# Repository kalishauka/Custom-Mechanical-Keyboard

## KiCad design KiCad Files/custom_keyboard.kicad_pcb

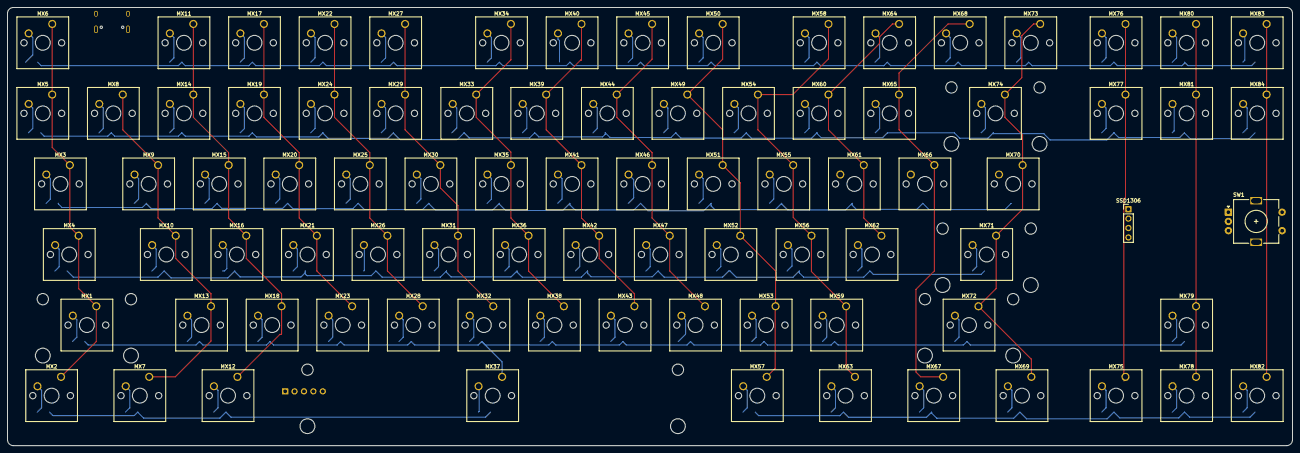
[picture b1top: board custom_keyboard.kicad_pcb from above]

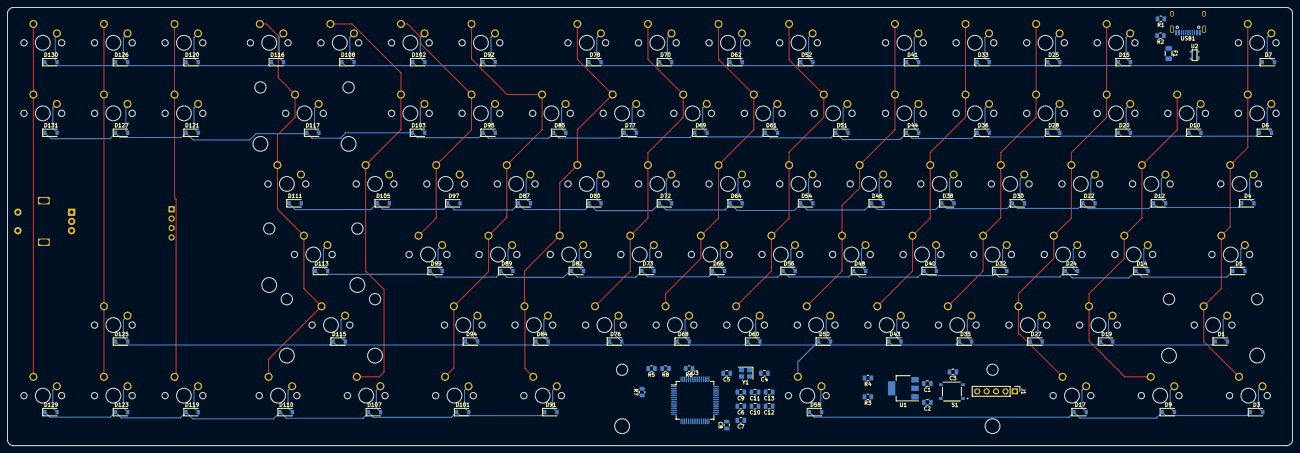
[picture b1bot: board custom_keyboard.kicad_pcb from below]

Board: 2 copper layers, 346.9 x 118.3 mm, 199 parts (113 on the bottom side), 130 nets.

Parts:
C1, C2: 10u; C_0805_2012Metric
C3: 0.1u; C_0805_2012Metric
C4, C5: 22p; C_0805_2012Metric
C6, C8: 4.7u; C_0805_2012Metric
C7, C9, C10, C11, C12, C13: 100n; C_0805_2012Metric
D1, D3, D4, D5, D6, D7, D9, D10, D12, D14, D15, D17, D19, D20, D22, D24, D25, D27, D28, D30, D32, D33, D35, D36, D38, D40, D41, D43, D44, D46, D48, D50, D51, D52, D54, D56, D58, D60, D61, D62, D64, D66, D68, D69, D70, D72, D73, D76, D77, D78, D80, D82, D84, D85, D87, D89, D91, D92, D94, D95, D97, D99, D101, D102, D103, D105, D107, D108, D110, D111, D113, D115, D116, D117, D119, D120, D121, D123, D125, D126, D127, D129, D130, D131: D_Small; D_SOD-123
F1: 500m; Fuse_1206_3216Metric
J1: Conn_01x05_Male; PinHeader_1x05_P2.54mm_Vertical
MX1: MX-NoLED L SHIFT; SW_Cherry_MX_2.25u_PCB
MX2: MX-NoLED CRTL; SW_Cherry_MX_1.25u_PCB
MX3: MX-NoLED Tab; SW_Cherry_MX_1.50u_PCB
MX4: MX-NoLED CAPS; SW_Cherry_MX_1.75u_PCB
MX5: MX-NoLED tilde; SW_Cherry_MX_1.00u_PCB
MX6: MX-NoLED ESC; SW_Cherry_MX_1.00u_PCB
MX7, MX63: MX-NoLED WIN; SW_Cherry_MX_1.25u_PCB
MX8: MX-NoLED 1; SW_Cherry_MX_1.00u_PCB
MX9: MX-NoLED Q; SW_Cherry_MX_1.00u_PCB
MX10: MX-NoLED A; SW_Cherry_MX_1.00u_PCB
MX11: MX-NoLED F1; SW_Cherry_MX_1.00u_PCB
MX12, MX57: MX-NoLED ALT; SW_Cherry_MX_1.25u_PCB
MX13: MX-NoLED Z; SW_Cherry_MX_1.00u_PCB
MX14: MX-NoLED 2; SW_Cherry_MX_1.00u_PCB
MX15: MX-NoLED W; SW_Cherry_MX_1.00u_PCB
MX16: MX-NoLED S; SW_Cherry_MX_1.00u_PCB
MX17: MX-NoLED F2; SW_Cherry_MX_1.00u_PCB
MX18: MX-NoLED X; SW_Cherry_MX_1.00u_PCB
MX19: MX-NoLED 3; SW_Cherry_MX_1.00u_PCB
MX20: MX-NoLED E; SW_Cherry_MX_1.00u_PCB
MX21: MX-NoLED D; SW_Cherry_MX_1.00u_PCB
MX22: MX-NoLED F3; SW_Cherry_MX_1.00u_PCB
MX23: MX-NoLED C; SW_Cherry_MX_1.00u_PCB
MX24: MX-NoLED 4; SW_Cherry_MX_1.00u_PCB
MX25: MX-NoLED R; SW_Cherry_MX_1.00u_PCB
MX26: MX-NoLED F; SW_Cherry_MX_1.00u_PCB
MX27: MX-NoLED F4; SW_Cherry_MX_1.00u_PCB
MX28: MX-NoLED V; SW_Cherry_MX_1.00u_PCB
MX29: MX-NoLED 5; SW_Cherry_MX_1.00u_PCB
MX30: MX-NoLED T; SW_Cherry_MX_1.00u_PCB
MX31: MX-NoLED G; SW_Cherry_MX_1.00u_PCB
MX32: MX-NoLED B; SW_Cherry_MX_1.00u_PCB
MX33: MX-NoLED 6; SW_Cherry_MX_1.00u_PCB
MX34: MX-NoLED F5; SW_Cherry_MX_1.00u_PCB
MX35: MX-NoLED Y; SW_Cherry_MX_1.00u_PCB
MX36: MX-NoLED H; SW_Cherry_MX_1.00u_PCB
MX37: MX-NoLED SPACE; SW_Cherry_MX_6.25u_PCB
MX38: MX-NoLED N; SW_Cherry_MX_1.00u_PCB
MX39: MX-NoLED 7; SW_Cherry_MX_1.00u_PCB
MX40: MX-NoLED F6; SW_Cherry_MX_1.00u_PCB
MX41: MX-NoLED U; SW_Cherry_MX_1.00u_PCB
MX42: MX-NoLED J; SW_Cherry_MX_1.00u_PCB
MX43: MX-NoLED M; SW_Cherry_MX_1.00u_PCB
MX44: MX-NoLED 8; SW_Cherry_MX_1.00u_PCB
MX45: MX-NoLED F7; SW_Cherry_MX_1.00u_PCB
MX46: MX-NoLED I; SW_Cherry_MX_1.00u_PCB
MX47: MX-NoLED K; SW_Cherry_MX_1.00u_PCB
MX48: MX-NoLED ,; SW_Cherry_MX_1.00u_PCB
MX49: MX-NoLED 9; SW_Cherry_MX_1.00u_PCB
MX50: MX-NoLED F8; SW_Cherry_MX_1.00u_PCB
MX51: MX-NoLED O; SW_Cherry_MX_1.00u_PCB
MX52: MX-NoLED L; SW_Cherry_MX_1.00u_PCB
MX53: MX-NoLED .; SW_Cherry_MX_1.00u_PCB
MX54: MX-NoLED 0; SW_Cherry_MX_1.00u_PCB
MX55: MX-NoLED P; SW_Cherry_MX_1.00u_PCB
MX56: MX-NoLED ;; SW_Cherry_MX_1.00u_PCB
MX58: MX-NoLED F9; SW_Cherry_MX_1.00u_PCB
MX59: MX-NoLED /; SW_Cherry_MX_1.00u_PCB
MX60: MX-NoLED dash; SW_Cherry_MX_1.00u_PCB
MX61: MX-NoLED [; SW_Cherry_MX_1.00u_PCB
MX62: MX-NoLED '; SW_Cherry_MX_1.00u_PCB
MX64: MX-NoLED F10; SW_Cherry_MX_1.00u_PCB
MX65: MX-NoLED =; SW_Cherry_MX_1.00u_PCB
MX66: MX-NoLED ]; SW_Cherry_MX_1.00u_PCB
MX67: MX-NoLED MENU; SW_Cherry_MX_1.25u_PCB
MX68: MX-NoLED F11; SW_Cherry_MX_1.00u_PCB
MX69: MX-NoLED CTRL; SW_Cherry_MX_1.25u_PCB
MX70: MX-NoLED \; SW_Cherry_MX_1.50u_PCB
MX71: MX-NoLED ENTER; SW_Cherry_MX_2.25u_PCB
MX72: MX-NoLED R SHIFT; SW_Cherry_MX_2.75u_PCB
MX73: MX-NoLED F12; SW_Cherry_MX_1.00u_PCB
MX74: MX-NoLED BACKSPACE; SW_Cherry_MX_2.00u_PCB
MX75: MX-NoLED LEFT; SW_Cherry_MX_1.00u_PCB
MX76: MX-NoLED Insert; SW_Cherry_MX_1.00u_PCB
MX77: MX-NoLED Delete; SW_Cherry_MX_1.00u_PCB
MX78: MX-NoLED DOWN; SW_Cherry_MX_1.00u_PCB
MX79: MX-NoLED UP; SW_Cherry_MX_1.00u_PCB
MX80: MX-NoLED Home; SW_Cherry_MX_1.00u_PCB
MX81: MX-NoLED End; SW_Cherry_MX_1.00u_PCB
MX82: MX-NoLED RIGHT; SW_Cherry_MX_1.00u_PCB
MX83: MX-NoLED PgUp; SW_Cherry_MX_1.00u_PCB
MX84: MX-NoLED PgDn; SW_Cherry_MX_1.00u_PCB
R1, R2: 5.1k; R_0805_2012Metric
R3, R4: 0; R_0805_2012Metric
R5: 4.7k; R_0805_2012Metric
R6: 10k; R_0805_2012Metric
R7, R8: 22; R_0805_2012Metric
S1: TS-1187A-B-A-B; SW_TS-1187A-B-A-B
SSD1306: Conn_01x04_Male; PinHeader_1x04_P2.54mm_Vertical
SW1: RotaryEncoder_Switch; RotaryEncoder_Alps_EC11E-Switch_Vertical_H20mm
U1: AMS1117; SOT-223-3_TabPin2
U2: PRTR5V0U2X; SOT143B
U3: STM32F401RCTx; LQFP-64_10x10mm_P0.5mm
USB1: HRO-TYPE-C-31-M-12
Y1: 16MHz; Crystal_SMD_3225-4Pin_3.2x2.5mm

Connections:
+3V3: C2.1, C6.1, C7.1, C9.1, C10.1, C11.1, C12.1, C13.1, J1.4, R3.1, R5.1, R6.1, SSD1306.2, U1.2 (VO), U3.1 (VBAT), U3.19 (VDD), U3.32 (VDD), U3.48 (VDD), U3.64 (VDD)
+5V: C1.1, F1.1, U1.3 (VI)
Col1: MX1.1 (COL), MX2.1 (COL), MX3.1 (COL), MX4.1 (COL), MX5.1 (COL), MX6.1 (COL), U3.37 (PC6)
Col2: MX7.1 (COL), MX8.1 (COL), MX9.1 (COL), MX10.1 (COL), MX13.1 (COL), U3.38 (PC7)
Col3: MX11.1 (COL), MX12.1 (COL), MX14.1 (COL), MX15.1 (COL), MX16.1 (COL), MX18.1 (COL), U3.39 (PC8)
Col4: MX17.1 (COL), MX19.1 (COL), MX20.1 (COL), MX21.1 (COL), MX23.1 (COL), U3.40 (PC9)
Col5: MX22.1 (COL), MX24.1 (COL), MX25.1 (COL), MX26.1 (COL), MX28.1 (COL), U3.51 (PC10)
Col6: MX27.1 (COL), MX29.1 (COL), MX30.1 (COL), MX31.1 (COL), MX32.1 (COL), U3.52 (PC11)
Col7: MX33.1 (COL), MX34.1 (COL), MX35.1 (COL), MX36.1 (COL), MX38.1 (COL), U3.53 (PC12)
Col8: MX39.1 (COL), MX40.1 (COL), MX41.1 (COL), MX42.1 (COL), MX43.1 (COL), U3.2 (PC13)
Col9: MX44.1 (COL), MX45.1 (COL), MX46.1 (COL), MX47.1 (COL), MX48.1 (COL), U3.3 (PC14)
Col10: MX49.1 (COL), MX50.1 (COL), MX51.1 (COL), MX52.1 (COL), MX53.1 (COL), MX57.1 (COL), U3.4 (PC15)
Col11: MX54.1 (COL), MX55.1 (COL), MX56.1 (COL), MX58.1 (COL), MX59.1 (COL), MX63.1 (COL), U3.14 (PA0)
Col12: MX60.1 (COL), MX61.1 (COL), MX62.1 (COL), MX64.1 (COL), U3.15 (PA1)
Col13: MX65.1 (COL), MX66.1 (COL), MX67.1 (COL), MX68.1 (COL), U3.16 (PA2)
Col14: MX69.1 (COL), MX70.1 (COL), MX71.1 (COL), MX72.1 (COL), MX73.1 (COL), MX74.1 (COL), U3.17 (PA3)
Col15: MX75.1 (COL), MX76.1 (COL), MX77.1 (COL), U3.20 (PA4)
Col16: MX78.1 (COL), MX79.1 (COL), MX80.1 (COL), MX81.1 (COL), U3.21 (PA5)
Col17: MX82.1 (COL), MX83.1 (COL), MX84.1 (COL), U3.22 (PA6)
D+: R8.2, U2.2 (IO1), USB1.6 (DP1), USB1.8 (DP2)
D-: R7.2, U2.3 (IO2), USB1.5 (DN2), USB1.7 (DN1)
ENC_A: SW1.A, U3.23 (PA7)
ENC_B: SW1.B, U3.41 (PA8)
ENC_SW: SW1.S1, U3.42 (PA9)
GND: C1.2, C2.2, C3.1, C4.1, C5.1, C6.2, C7.2, C8.2, C9.2, C10.2, C11.2, C12.2, C13.2, J1.1, R1.2, R2.2, R4.2, S1.A, S1.B, SSD1306.1, SW1.C, SW1.S2, U1.1 (ADJ), U2.1 (GND), U3.12 (VSSA), U3.18 (VSS), U3.31 (VSS), U3.47 (VSS), U3.63 (VSS), USB1.1 (GND), USB1.12 (GND), USB1.13 (SHIELD), Y1.2, Y1.4
unnamed: C5.2, U3.6 (PH1), Y1.3
unnamed: C8.1, U3.30 (VCAP1)
unnamed: D1.2 (A), MX1.2 (ROW)
unnamed: D3.2 (A), MX2.2 (ROW)
unnamed: D4.2 (A), MX3.2 (ROW)
unnamed: D5.2 (A), MX4.2 (ROW)
unnamed: D6.2 (A), MX5.2 (ROW)
unnamed: D7.2 (A), MX6.2 (ROW)
unnamed: D9.2 (A), MX7.2 (ROW)
unnamed: D10.2 (A), MX8.2 (ROW)
unnamed: D12.2 (A), MX9.2 (ROW)
unnamed: D14.2 (A), MX10.2 (ROW)
unnamed: D15.2 (A), MX11.2 (ROW)
unnamed: D17.2 (A), MX12.2 (ROW)
unnamed: D19.2 (A), MX13.2 (ROW)
unnamed: D20.2 (A), MX14.2 (ROW)
unnamed: D22.2 (A), MX15.2 (ROW)
unnamed: D24.2 (A), MX16.2 (ROW)
unnamed: D25.2 (A), MX17.2 (ROW)
unnamed: D27.2 (A), MX18.2 (ROW)
unnamed: D28.2 (A), MX19.2 (ROW)
unnamed: D30.2 (A), MX20.2 (ROW)
unnamed: D32.2 (A), MX21.2 (ROW)
unnamed: D33.2 (A), MX22.2 (ROW)
unnamed: D35.2 (A), MX23.2 (ROW)
unnamed: D36.2 (A), MX24.2 (ROW)
unnamed: D38.2 (A), MX25.2 (ROW)
unnamed: D40.2 (A), MX26.2 (ROW)
unnamed: D41.2 (A), MX27.2 (ROW)
unnamed: D43.2 (A), MX28.2 (ROW)
unnamed: D44.2 (A), MX29.2 (ROW)
unnamed: D46.2 (A), MX30.2 (ROW)
unnamed: D48.2 (A), MX31.2 (ROW)
unnamed: D50.2 (A), MX32.2 (ROW)
unnamed: D51.2 (A), MX33.2 (ROW)
unnamed: D52.2 (A), MX34.2 (ROW)
unnamed: D54.2 (A), MX35.2 (ROW)
unnamed: D56.2 (A), MX36.2 (ROW)
unnamed: D58.2 (A), MX37.2 (ROW)
unnamed: D60.2 (A), MX38.2 (ROW)
unnamed: D61.2 (A), MX39.2 (ROW)
unnamed: D62.2 (A), MX40.2 (ROW)
unnamed: D64.2 (A), MX41.2 (ROW)
unnamed: D66.2 (A), MX42.2 (ROW)
unnamed: D68.2 (A), MX43.2 (ROW)
unnamed: D69.2 (A), MX44.2 (ROW)
unnamed: D70.2 (A), MX45.2 (ROW)
unnamed: D72.2 (A), MX46.2 (ROW)
unnamed: D73.2 (A), MX47.2 (ROW)
unnamed: D76.2 (A), MX48.2 (ROW)
unnamed: D77.2 (A), MX49.2 (ROW)
unnamed: D78.2 (A), MX50.2 (ROW)
unnamed: D80.2 (A), MX51.2 (ROW)
unnamed: D82.2 (A), MX52.2 (ROW)
unnamed: D84.2 (A), MX53.2 (ROW)
unnamed: D85.2 (A), MX54.2 (ROW)
unnamed: D87.2 (A), MX55.2 (ROW)
unnamed: D89.2 (A), MX56.2 (ROW)
unnamed: D91.2 (A), MX57.2 (ROW)
unnamed: D92.2 (A), MX58.2 (ROW)
unnamed: D94.2 (A), MX59.2 (ROW)
unnamed: D95.2 (A), MX60.2 (ROW)
unnamed: D97.2 (A), MX61.2 (ROW)
unnamed: D99.2 (A), MX62.2 (ROW)
unnamed: D101.2 (A), MX63.2 (ROW)
unnamed: D102.2 (A), MX64.2 (ROW)
unnamed: D103.2 (A), MX65.2 (ROW)
unnamed: D105.2 (A), MX66.2 (ROW)
unnamed: D107.2 (A), MX67.2 (ROW)
unnamed: D108.2 (A), MX68.2 (ROW)
unnamed: D110.2 (A), MX69.2 (ROW)
unnamed: D111.2 (A), MX70.2 (ROW)
unnamed: D113.2 (A), MX71.2 (ROW)
unnamed: D115.2 (A), MX72.2 (ROW)
unnamed: D116.2 (A), MX73.2 (ROW)
unnamed: D117.2 (A), MX74.2 (ROW)
unnamed: D119.2 (A), MX75.2 (ROW)
unnamed: D120.2 (A), MX76.2 (ROW)
unnamed: D121.2 (A), MX77.2 (ROW)
unnamed: D123.2 (A), MX78.2 (ROW)
unnamed: D125.2 (A), MX79.2 (ROW)
unnamed: D126.2 (A), MX80.2 (ROW)
unnamed: D127.2 (A), MX81.2 (ROW)
unnamed: D129.2 (A), MX82.2 (ROW)
unnamed: D130.2 (A), MX83.2 (ROW)
unnamed: D131.2 (A), MX84.2 (ROW)
unnamed: R1.1, USB1.10 (CC2)
unnamed: R2.1, USB1.4 (CC1)
unnamed: R3.2, R4.1, U3.60 (BOOT0)
unnamed: R7.1, U3.44 (PA11)
unnamed: R8.1, U3.45 (PA12)
unnamed: C3.2, S1.C, S1.D, U3.7 (NRST)
unnamed: C4.2, U3.5 (PH0), Y1.1
Row1: D7.1 (K), D15.1 (K), D25.1 (K), D33.1 (K), D41.1 (K), D52.1 (K), D62.1 (K), D70.1 (K), D78.1 (K), D92.1 (K), D102.1 (K), D108.1 (K), D116.1 (K), D120.1 (K), D126.1 (K), D130.1 (K), U3.8 (PC0)
Row2: D6.1 (K), D10.1 (K), D20.1 (K), D28.1 (K), D36.1 (K), D44.1 (K), D51.1 (K), D61.1 (K), D69.1 (K), D77.1 (K), D85.1 (K), D95.1 (K), D103.1 (K), D117.1 (K), D121.1 (K), D127.1 (K), D131.1 (K), U3.9 (PC1)
Row3: D4.1 (K), D12.1 (K), D22.1 (K), D30.1 (K), D38.1 (K), D46.1 (K), D54.1 (K), D64.1 (K), D72.1 (K), D80.1 (K), D87.1 (K), D97.1 (K), D105.1 (K), D111.1 (K), U3.10 (PC2)
Row4: D5.1 (K), D14.1 (K), D24.1 (K), D32.1 (K), D40.1 (K), D48.1 (K), D56.1 (K), D66.1 (K), D73.1 (K), D82.1 (K), D89.1 (K), D99.1 (K), D113.1 (K), U3.11 (PC3)
Row5: D1.1 (K), D19.1 (K), D27.1 (K), D35.1 (K), D43.1 (K), D50.1 (K), D60.1 (K), D68.1 (K), D76.1 (K), D84.1 (K), D94.1 (K), D115.1 (K), D125.1 (K), MX37.1 (COL), U3.24 (PC4)
Row6: D3.1 (K), D9.1 (K), D17.1 (K), D58.1 (K), D91.1 (K), D101.1 (K), D107.1 (K), D110.1 (K), D119.1 (K), D123.1 (K), D129.1 (K), U3.25 (PC5)
SCL: R5.2, SSD1306.3, U3.58 (PB6)
SDA: R6.2, SSD1306.4, U3.59 (PB7)
SWCLK: J1.2, U3.49 (PA14)
SWDIO: J1.3, U3.46 (PA13)
SWO: J1.5, U3.55 (PB3)
VBUS: F1.2, U2.4 (VCC), USB1.2 (VBUS), USB1.11 (VBUS)

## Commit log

2022-07-18 added .gitignore
2022-07-18 Added KiCad files
2022-08-29 keys in schematic
2022-08-30 Col and row routing
2022-08-30 Added outline
2022-08-31 finished routing
2022-09-25 Added the 3D Models for all components
